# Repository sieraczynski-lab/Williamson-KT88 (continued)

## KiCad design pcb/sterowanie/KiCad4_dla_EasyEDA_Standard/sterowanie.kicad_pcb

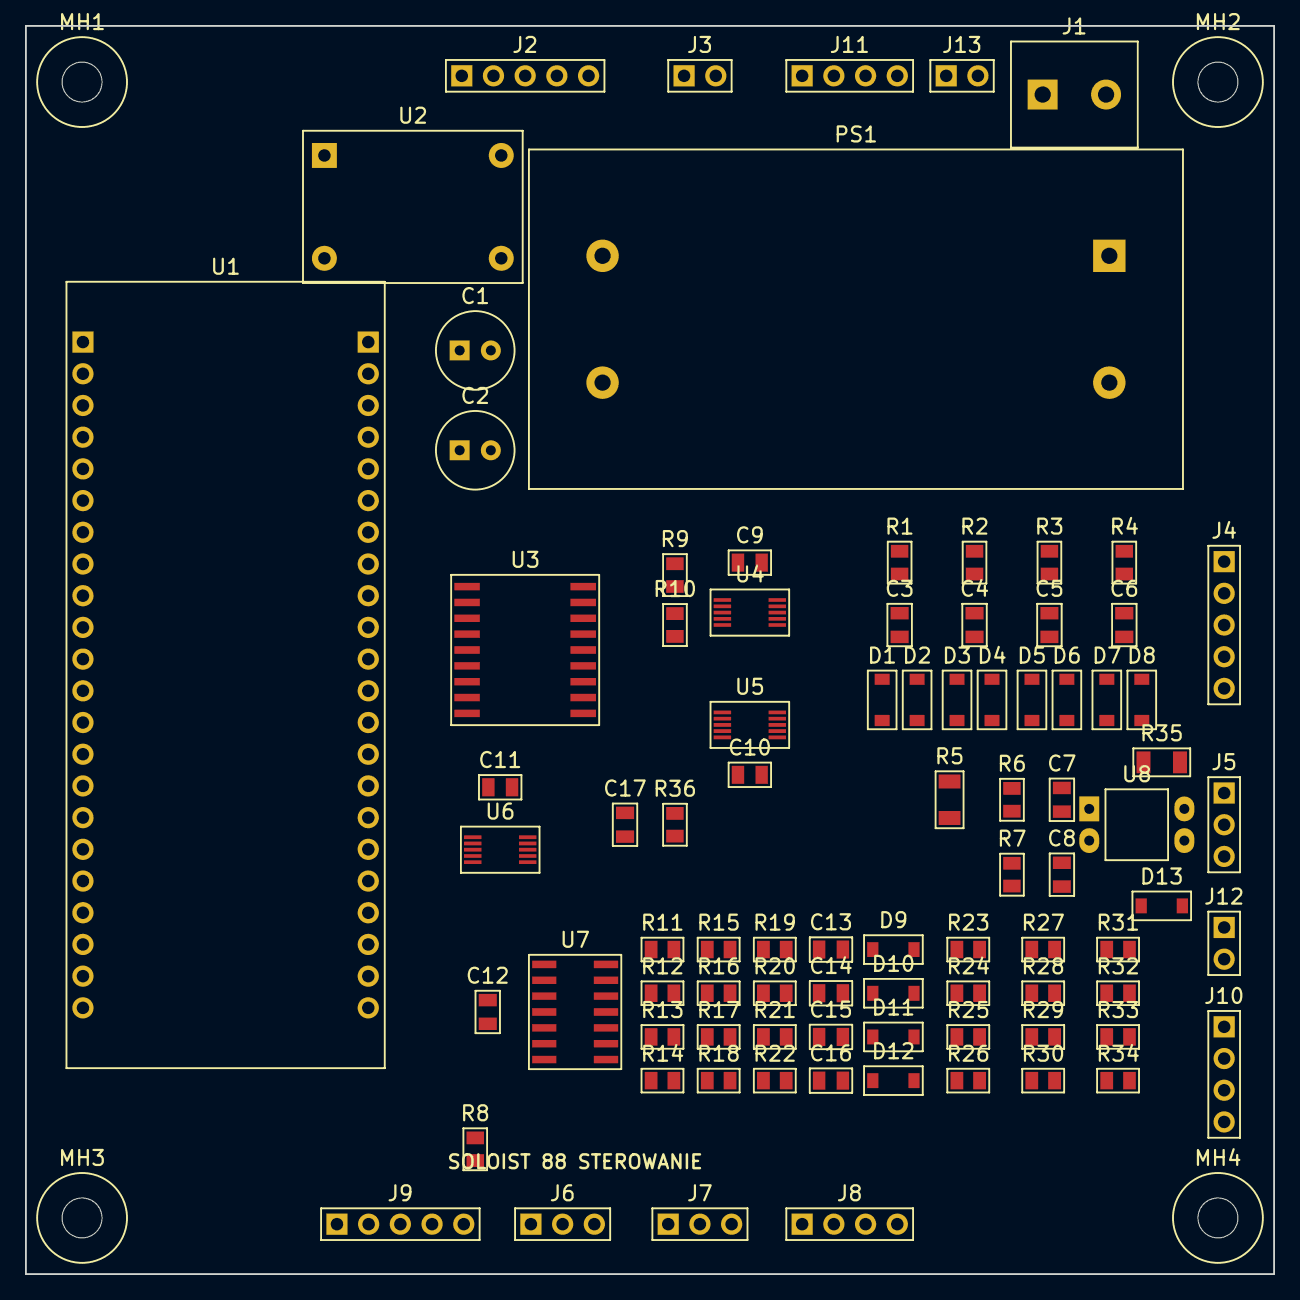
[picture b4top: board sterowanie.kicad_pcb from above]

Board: 2 copper layers, 100.0 x 100.0 mm, 92 parts (0 on the bottom side), 68 nets, no tracks yet.

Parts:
C1: 100u/25V; CP_Radial_D6.3_P2.5
C2: 100u/16V; CP_Radial_D6.3_P2.5
C3, C4, C5, C6, C7, C8: 1u; C_0805_2012Metric_V
C9, C10, C11: 100n; C_0805_2012Metric
C12, C17: 100n; C_0805_2012Metric_V
C13, C14, C15, C16: 1u; C_0805_2012Metric
D1, D2, D3, D4, D5, D6, D7, D8: 1N4148W; D_SOD-123_V
D9, D10, D11, D12, D13: 1N4148W; D_SOD-123
J1: 230V_IN; TerminalBlock_1x02_P5.08
J2: RELAY; PinHeader_1x05_P2.54_H
J3: MUTE; PinHeader_1x02_P2.54_H
J4: IK; PinHeader_1x05_P2.54
J5: SENSE; PinHeader_1x03_P2.54
J6: DS18B20; PinHeader_1x03_P2.54_H
J7: IR; PinHeader_1x03_P2.54_H
J8: WYSWIETLACZ; PinHeader_1x04_P2.54_H
J9: ENKODER; PinHeader_1x05_P2.54_H
J10: BIAS_KOR; PinHeader_1x04_P2.54
J11: UL_TRIODA; PinHeader_1x04_P2.54_H
J12: TRIGGER; PinHeader_1x02_P2.54
J13: GLOSNIKI; PinHeader_1x02_P2.54_H
MH1, MH2, MH3, MH4: M3; MountingHole_M3
PS1: IRM-15-12; MeanWell_IRM-15_approx
R1, R2, R3, R4, R6, R7, R36: 10k; R_0805_2012Metric_V
R5: 330k 1206; R_1206_3216Metric_V
R8, R9, R10: 4k7; R_0805_2012Metric_V
R11, R12, R13, R14, R19, R20, R21, R22: 10k; R_0805_2012Metric
R15, R16, R17, R18: 20k; R_0805_2012Metric
R23, R24, R25, R26: 68k; R_0805_2012Metric
R27, R28, R29, R30: 33k; R_0805_2012Metric
R31, R32, R33, R34: 1k; R_0805_2012Metric
R35: 1k 1206; R_1206_3216Metric
U1: ESP32-S3-DevKitC-1
U2: DC-DC 5V mini; DCDC_5V_mini_14.17x8.24
U3: ULN2803G-S18-R; SOIC-18W_7.5x11.6mm_P1.27mm
U4: ADS1115IDGSR 0x48; MSOP-10_3x3mm_P0.5mm
U5: ADS1115IDGSR 0x49; MSOP-10_3x3mm_P0.5mm
U6: MCP4728-E/UN; MSOP-10_3x3mm_P0.5mm
U7: LM324DR; SOIC-14_3.9x8.7mm_P1.27mm
U8: PC817; DIP-4_W7.62

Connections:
3V3: C9.1, C10.1, C11.1, D2.1, D4.1, D6.1, D8.1, J6.1, J7.1, J8.1, R6.2, R8.1, R9.1, R10.1, R36.1, U1.L1, U1.L2, U4.8, U5.1, U5.5, U5.8, U6.1
+5V: C2.1, U1.L21, U2.3
+12V: C1.1, C12.1, J2.1, J3.1, J11.1, J11.3, J13.1, PS1.4, U2.2, U3.10, U7.4
BI_L1: J10.1, R31.2
BI_L2: J10.2, R32.2
BI_R1: J10.3, R33.2
BI_R2: J10.4, R34.2
BTN: J9.4, U1.L9
DACF_L1: C13.1, R19.2, U7.3
DACF_L2: C14.1, R20.2, U7.5
DACF_R1: C15.1, R21.2, U7.10
DACF_R2: C16.1, R22.2, U7.12
DAC_L1: R19.1, U6.6
DAC_L2: R20.1, U6.7
DAC_R1: R21.1, U6.8
DAC_R2: R22.1, U6.9
DQ: J6.2, R8.2, U1.L4
DRV1: U1.L16, U3.1
DRV2: U1.L17, U3.2
DRV3: U1.L18, U3.3
DRV4: U1.L19, U3.4
DRV5: U1.L20, U3.5
DRV6: U1.L10, U3.6
DRV7: U1.L11, U3.7
ENC_A: J9.1, U1.L6
ENC_B: J9.2, U1.L7
ENC_SW: J9.3, U1.L8
FB_L1: R11.1, R15.2, U7.2
FB_L2: R12.1, R16.2, U7.6
FB_R1: R13.1, R17.2, U7.9
FB_R2: R14.1, R18.2, U7.13
GND: C1.2, C2.2, C3.2, C4.2, C5.2, C6.2, C7.2, C8.2, C9.2, C10.2, C11.2, C12.2, C13.2, C14.2, C15.2, C16.2, C17.2, D1.2, D3.2, D5.2, D7.2, D9.2, D10.2, D11.2, D12.2, J4.5, J5.3, J6.3, J7.3, J8.2, J9.5, PS1.3, R11.2, R12.2, R13.2, R14.2, U1.L22, U1.R1, U1.R21, U1.R22, U2.1, U2.4, U3.8, U3.9, U4.1, U4.3, U5.3, U6.4, U6.10, U7.11, U8.3
HV_F: C8.1, R7.2, U5.6
HV_SENSE: J5.2, R7.1
IK_L1: J4.1, R1.1
IK_L1F: C3.1, D1.1, D2.2, R1.2, U4.4
IK_L2: J4.2, R2.1
IK_L2F: C4.1, D3.1, D4.2, R2.2, U4.5
IK_R1: J4.3, R3.1
IK_R1F: C5.1, D5.1, D6.2, R3.2, U4.6
IK_R2: J4.4, R4.1
IK_R2F: C6.1, D7.1, D8.2, R4.2, U4.7
IR: J7.2, U1.L5
L_PS: J1.1, PS1.1
MUTE: J3.2, U3.14
N_PS: J1.2, PS1.2
OA_L1: D9.1, R15.1, R23.1, U7.1
OA_L2: D10.1, R16.1, R24.1, U7.7
OA_R1: D11.1, R17.1, R25.1, U7.8
OA_R2: D12.1, R18.1, R26.1, U7.14
OPTO_A: D13.1, R35.2, U8.1
RLY1: J2.2, U3.18
RLY2: J2.3, U3.17
RLY3: J2.4, U3.16
RLY4: J2.5, U3.15
RLY_SPK: J13.2, U3.12
RLY_UL: J11.2, J11.4, U3.13
SCL: J8.3, R10.2, U1.L15, U4.10, U5.10, U6.2
SDA: J8.4, R9.2, U1.L12, U4.9, U5.9, U6.3
S_L1: R23.2, R27.1, R31.1
S_L2: R24.2, R28.1, R32.1
S_R1: R25.2, R29.1, R33.1
S_R2: R26.2, R30.1, R34.1
TRIG_IN: C17.1, R36.2, U1.R4, U8.4
TRIG_N: D13.2, J12.2, U8.2
TRIG_P: J12.1, R35.1
VBIAS: J5.1, R5.1, R27.2, R28.2, R29.2, R30.2
VB_F: C7.1, R5.2, R6.1, U5.4

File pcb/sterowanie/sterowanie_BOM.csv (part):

Oznaczenie;Wartosc;Footprint;Strona;X [mm];Y [mm];Grupa;LCSC;Uwagi
U1;ESP32-S3-DevKitC-1;ESP32-S3-DevKitC-1;GORA;16.00;52.00;ESP32;;na listwach zenskich
J1;230V_IN;TerminalBlock_1x02_P5.08;GORA;84.00;5.50;ZASILANIE 12 V / 5 V;;zlacze srubowe 230 V: z zasilacz_siec J3 (za F2)
PS1;IRM-15-12;MeanWell_IRM-15_approx;GORA;66.50;23.50;ZASILANIE 12 V / 5 V;;Mean Well IRM-15-12, 12 V / 1,25 A
U2;DC-DC 5V mini;DCDC_5V_mini_14.17x8.24;GORA;31.00;14.50;ZASILANIE 12 V / 5 V;;"mini przetwornica step-down, stale 5 V, min. 1 A; 1 -IN, 2 +IN, 3 OUT+, 4 OUT-"
C1;100u/25V;CP_Radial_D6.3_P2.5;GORA;36.00;26.00;ZASILANIE 12 V / 5 V;;
C2;100u/16V;CP_Radial_D6.3_P2.5;GORA;36.00;34.00;ZASILANIE 12 V / 5 V;;
U3;ULN2803G-S18-R;SOIC-18W_7.5x11.6mm_P1.27mm;GORA;40.00;50.00;STEROWNIK PRZEKAZNIKOW;C33924;UTC ULN2803G-S18-R, SOP-18 (7,5 mm) - LCSC C33924
J2;RELAY;PinHeader_1x05_P2.54_H;GORA;40.00;4.00;STEROWNIK PRZEKAZNIKOW;;"do plytek zasilacza (piny 1,2,3 -> siec; 1,4,5 -> HV)"
J3;MUTE;PinHeader_1x02_P2.54_H;GORA;54.00;4.00;STEROWNIK PRZEKAZNIKOW;;przekaznik MUTE w przedwzmacniaczu
J11;UL_TRIODA;PinHeader_1x04_P2.54_H;GORA;66.00;4.00;STEROWNIK PRZEKAZNIKOW;;1-2 plytka UL kanalu L, 3-4 kanalu P (J3 na plytce UL)
J13;GLOSNIKI;PinHeader_1x02_P2.54_H;GORA;75.00;4.00;STEROWNIK PRZEKAZNIKOW;;cewki przelacznika glosnikow (plytka glosniki J7)
J12;TRIGGER;PinHeader_1x02_P2.54;GORA;96.00;73.50;WEJSCIE TRIGGER 12 V;;z gniazda jack 3,5 mm na tylnej sciance (izolowanego od obudowy): 1 koncowka (+12 V), 2 tulejka
R35;1k 1206;R_1206_3216Metric;GORA;91.00;59.00;WEJSCIE TRIGGER 12 V;C4410;ok. 10 mA przy 12 V
D13;1N4148W;D_SOD-123;GORA;91.00;70.50;WEJSCIE TRIGGER 12 V;C81598;ochrona przed odwrotna polaryzacja
U8;PC817;DIP-4_W7.62;GORA;89.00;64.00;WEJSCIE TRIGGER 12 V;;transoptor - masa Marantza oddzielona od masy Lampy
R36;10k;R_0805_2012Metric_V;GORA;52.00;64.00;WEJSCIE TRIGGER 12 V;C17414;"podciaganie; TRIG_IN = 0 gdy trigger aktywny"
C17;100n;C_0805_2012Metric_V;GORA;48.00;64.00;WEJSCIE TRIGGER 12 V;C49678;filtr zaklocen
U4;ADS1115IDGSR 0x48;MSOP-10_3x3mm_P0.5mm;GORA;58.00;47.00;POMIARY ADC;C37593;ADDR do GND
U5;ADS1115IDGSR 0x49;MSOP-10_3x3mm_P0.5mm;GORA;58.00;56.00;POMIARY ADC;C37593;ADDR do VDD
C9;100n;C_0805_2012Metric;GORA;58.00;43.00;POMIARY ADC;C49678;przy U4
C10;100n;C_0805_2012Metric;GORA;58.00;60.00;POMIARY ADC;C49678;przy U5
R9;4k7;R_0805_2012Metric_V;GORA;52.00;44.00;POMIARY ADC;C17673;podciaganie I2C
R10;4k7;R_0805_2012Metric_V;GORA;52.00;48.00;POMIARY ADC;C17673;podciaganie I2C
U6;MCP4728-E/UN;MSOP-10_3x3mm_P0.5mm;GORA;38.00;66.00;KOREKTA BIASU (DAC);C108207;"I2C 0x60, Vref = VDD 3,3 V; LDAC do masy"
C11;100n;C_0805_2012Metric;GORA;38.00;61.00;KOREKTA BIASU (DAC);C49678;przy U6
U7;LM324DR;SOIC-14_3.9x8.7mm_P1.27mm;GORA;44.00;79.00;KOREKTA BIASU (DAC);C7943;wzmocnienie x3: 0-3,3 V -> 0-9,9 V
C12;100n;C_0805_2012Metric_V;GORA;37.00;79.00;KOREKTA BIASU (DAC);C49678;przy U7
R1;10k;R_0805_2012Metric_V;GORA;70.00;43.00;FILTRY WEJSC;C17414;
C3;1u;C_0805_2012Metric_V;GORA;70.00;48.00;FILTRY WEJSC;C28323;X7R 50 V
D1;1N4148W;D_SOD-123_V;GORA;68.60;54.00;FILTRY WEJSC;C81598;zacisk do masy
D2;1N4148W;D_SOD-123_V;GORA;71.40;54.00;FILTRY WEJSC;C81598;zacisk do 3V3
R2;10k;R_0805_2012Metric_V;GORA;76.00;43.00;FILTRY WEJSC;C17414;
C4;1u;C_0805_2012Metric_V;GORA;76.00;48.00;FILTRY WEJSC;C28323;X7R 50 V
D3;1N4148W;D_SOD-123_V;GORA;74.60;54.00;FILTRY WEJSC;C81598;zacisk do masy
D4;1N4148W;D_SOD-123_V;GORA;77.40;54.00;FILTRY WEJSC;C81598;zacisk do 3V3
R3;10k;R_0805_2012Metric_V;GORA;82.00;43.00;FILTRY WEJSC;C17414;
C5;1u;C_0805_2012Metric_V;GORA;82.00;48.00;FILTRY WEJSC;C28323;X7R 50 V
D5;1N4148W;D_SOD-123_V;GORA;80.60;54.00;FILTRY WEJSC;C81598;zacisk do masy
D6;1N4148W;D_SOD-123_V;GORA;83.40;54.00;FILTRY WEJSC;C81598;zacisk do 3V3
R4;10k;R_0805_2012Metric_V;GORA;88.00;43.00;FILTRY WEJSC;C17414;
C6;1u;C_0805_2012Metric_V;GORA;88.00;48.00;FILTRY WEJSC;C28323;X7R 50 V
D7;1N4148W;D_SOD-123_V;GORA;86.60;54.00;FILTRY WEJSC;C81598;zacisk do masy
D8;1N4148W;D_SOD-123_V;GORA;89.40;54.00;FILTRY WEJSC;C81598;zacisk do 3V3
R11;10k;R_0805_2012Metric;GORA;51.00;74.00;KOREKTA BIASU (DAC);C17414;wzmocnienie
R15;20k;R_0805_2012Metric;GORA;55.50;74.00;KOREKTA BIASU (DAC);C4328;wzmocnienie
R19;10k;R_0805_2012Metric;GORA;60.00;74.00;KOREKTA BIASU (DAC);C17414;filtr RC przed LM324 (10k / 1u = 10 ms)
C13;1u;C_0805_2012Metric;GORA;64.50;74.00;KOREKTA BIASU (DAC);C28323;filtr RC
D9;1N4148W;D_SOD-123;GORA;69.50;74.00;KOREKTA BIASU (DAC);C81598;zacisk wyjscia LM324: bez 12 V nie schodzi ponizej masy
R23;68k;R_0805_2012Metric;GORA;75.50;74.00;KOREKTA BIASU (DAC);C17801;przesuwnik poziomu (0-9,9 V -> ok. -54...-51 V)
R27;33k;R_0805_2012Metric;GORA;81.50;74.00;KOREKTA BIASU (DAC);C17633;przesuwnik poziomu, do szyny biasu
R31;1k;R_0805_2012Metric;GORA;87.50;74.00;KOREKTA BIASU (DAC);C17513;wyjscie do wezla biasu (ochrona przy zwarciu przewodu)
R12;10k;R_0805_2012Metric;GORA;51.00;77.50;KOREKTA BIASU (DAC);C17414;wzmocnienie
R16;20k;R_0805_2012Metric;GORA;55.50;77.50;KOREKTA BIASU (DAC);C4328;wzmocnienie
R20;10k;R_0805_2012Metric;GORA;60.00;77.50;KOREKTA BIASU (DAC);C17414;filtr RC przed LM324 (10k / 1u = 10 ms)
C14;1u;C_0805_2012Metric;GORA;64.50;77.50;KOREKTA BIASU (DAC);C28323;filtr RC
D10;1N4148W;D_SOD-123;GORA;69.50;77.50;KOREKTA BIASU (DAC);C81598;zacisk wyjscia LM324: bez 12 V nie schodzi ponizej masy
R24;68k;R_0805_2012Metric;GORA;75.50;77.50;KOREKTA BIASU (DAC);C17801;przesuwnik poziomu (0-9,9 V -> ok. -54...-51 V)
R28;33k;R_0805_2012Metric;GORA;81.50;77.50;KOREKTA BIASU (DAC);C17633;przesuwnik poziomu, do szyny biasu
R32;1k;R_0805_2012Metric;GORA;87.50;77.50;KOREKTA BIASU (DAC);C17513;wyjscie do wezla biasu (ochrona przy zwarciu przewodu)
R13;10k;R_0805_2012Metric;GORA;51.00;81.00;KOREKTA BIASU (DAC);C17414;wzmocnienie
R17;20k;R_0805_2012Metric;GORA;55.50;81.00;KOREKTA BIASU (DAC);C4328;wzmocnienie
R21;10k;R_0805_2012Metric;GORA;60.00;81.00;KOREKTA BIASU (DAC);C17414;filtr RC przed LM324 (10k / 1u = 10 ms)
C15;1u;C_0805_2012Metric;GORA;64.50;81.00;KOREKTA BIASU (DAC);C28323;filtr RC
D11;1N4148W;D_SOD-123;GORA;69.50;81.00;KOREKTA BIASU (DAC);C81598;zacisk wyjscia LM324: bez 12 V nie schodzi ponizej masy
R25;68k;R_0805_2012Metric;GORA;75.50;81.00;KOREKTA BIASU (DAC);C17801;przesuwnik poziomu (0-9,9 V -> ok. -54...-51 V)
R29;33k;R_0805_2012Metric;GORA;81.50;81.00;KOREKTA BIASU (DAC);C17633;przesuwnik poziomu, do szyny biasu
R33;1k;R_0805_2012Metric;GORA;87.50;81.00;KOREKTA BIASU (DAC);C17513;wyjscie do wezla biasu (ochrona przy zwarciu przewodu)
R14;10k;R_0805_2012Metric;GORA;51.00;84.50;KOREKTA BIASU (DAC);C17414;wzmocnienie
R18;20k;R_0805_2012Metric;GORA;55.50;84.50;KOREKTA BIASU (DAC);C4328;wzmocnienie
R22;10k;R_0805_2012Metric;GORA;60.00;84.50;KOREKTA BIASU (DAC);C17414;filtr RC przed LM324 (10k / 1u = 10 ms)
C16;1u;C_0805_2012Metric;GORA;64.50;84.50;KOREKTA BIASU (DAC);C28323;filtr RC
D12;1N4148W;D_SOD-123;GORA;69.50;84.50;KOREKTA BIASU (DAC);C81598;zacisk wyjscia LM324: bez 12 V nie schodzi ponizej masy
R26;68k;R_0805_2012Metric;GORA;75.50;84.50;KOREKTA BIASU (DAC);C17801;przesuwnik poziomu (0-9,9 V -> ok. -54...-51 V)
R30;33k;R_0805_2012Metric;GORA;81.50;84.50;KOREKTA BIASU (DAC);C17633;przesuwnik poziomu, do szyny biasu
R34;1k;R_0805_2012Metric;GORA;87.50;84.50;KOREKTA BIASU (DAC);C17513;wyjscie do wezla biasu (ochrona przy zwarciu przewodu)
R5;330k 1206;R_1206_3216Metric_V;GORA;74.00;62.00;FILTRY WEJSC;C17929;pomiar -78 V
R6;10k;R_0805_2012Metric_V;GORA;79.00;62.00;FILTRY WEJSC;C17414;przesuniecie do 3V3
C7;1u;C_0805_2012Metric_V;GORA;83.00;62.00;FILTRY WEJSC;C28323;
R7;10k;R_0805_2012Metric_V;GORA;79.00;68.00;FILTRY WEJSC;C17414;
C8;1u;C_0805_2012Metric_V;GORA;83.00;68.00;FILTRY WEJSC;C28323;
R8;4k7;R_0805_2012Metric_V;GORA;36.00;90.00;ESP32;C17673;pull-up DS18B20
J4;IK;PinHeader_1x05_P2.54;GORA;96.00;48.00;ZLACZA;;z rezystorow 10R przy KT88
J5;SENSE;PinHeader_1x03_P2.54;GORA;96.00;64.00;ZLACZA;;
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
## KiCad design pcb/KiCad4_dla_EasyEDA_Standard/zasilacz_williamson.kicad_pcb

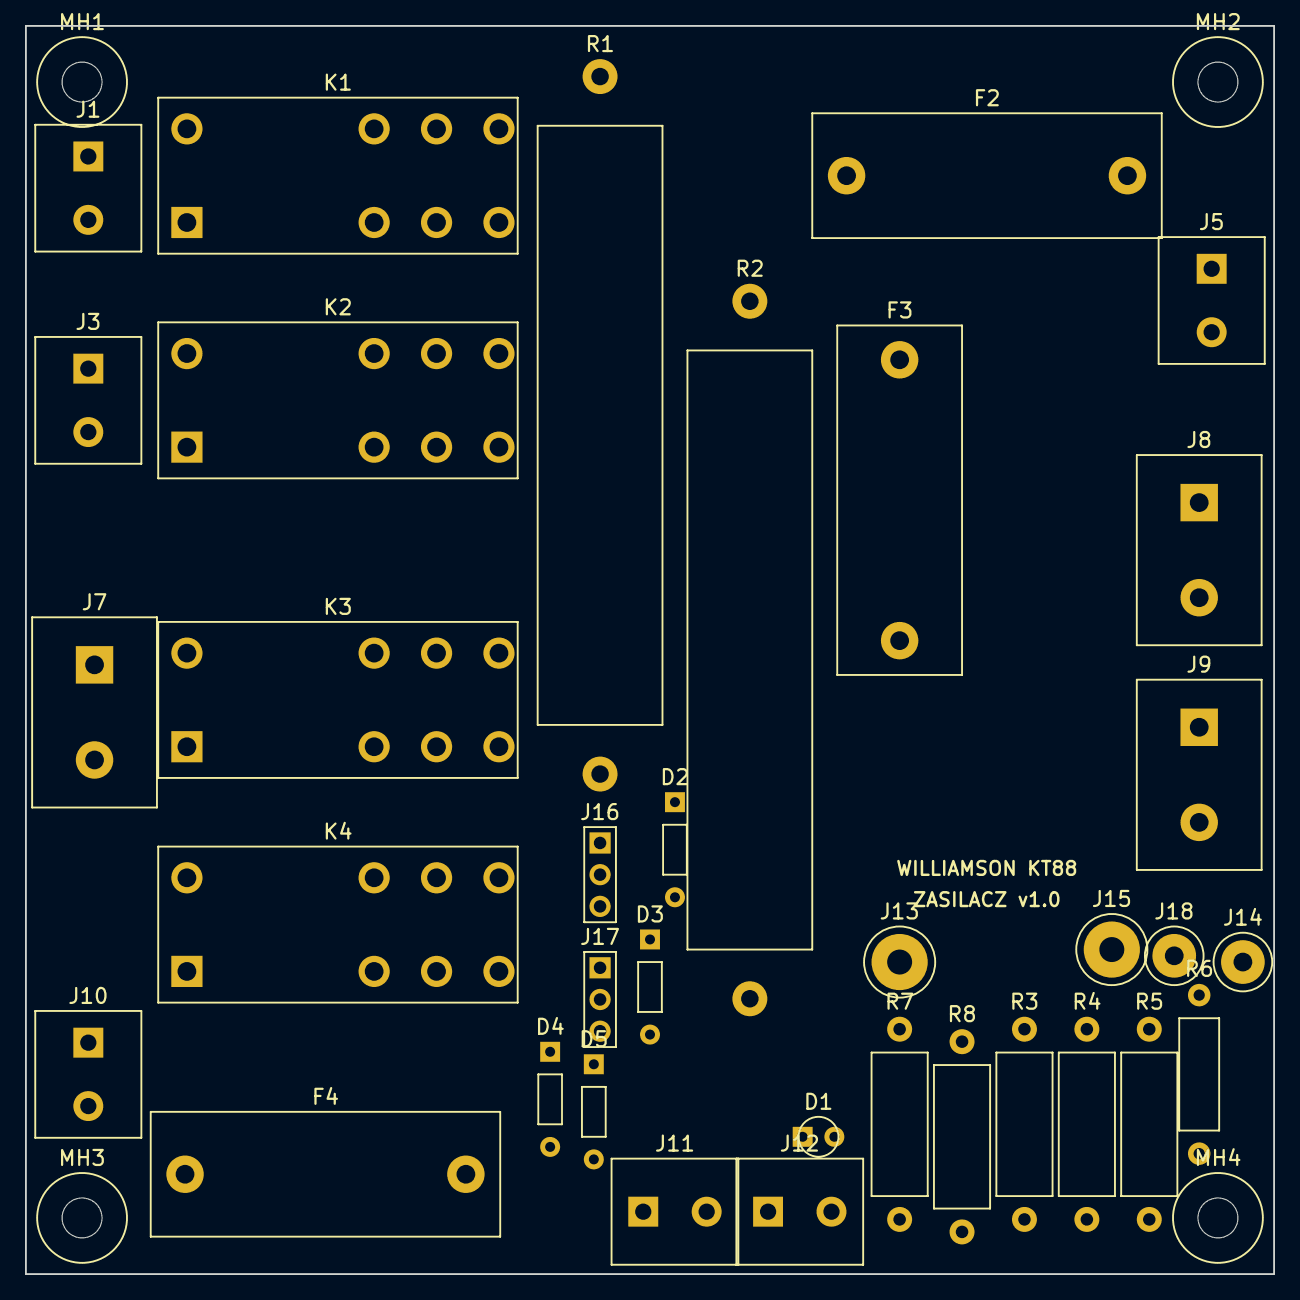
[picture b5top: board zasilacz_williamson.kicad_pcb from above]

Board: 2 copper layers, 100.0 x 100.0 mm, 39 parts (0 on the bottom side), 26 nets, no tracks yet.

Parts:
D1: LED HV czerwona; LED_D3.0_P2.54
D2, D3, D4, D5: 1N4148; D_DO-35_P7.62_V
F2: T500mA 250V; Fuseholder_5x20_Closed_P22.5
F3: T1A 500V; Fuseholder_5x20_Closed_P22.5_V
F4: T100mA 250V; Fuseholder_5x20_Closed_P22.5
J1: SIEC; TerminalBlock_1x02_P5.08_V
J3: PS1; TerminalBlock_1x02_P5.08_V
J5: TR1_PRI; TerminalBlock_1x02_P5.08_V
J7: S1_IN; TerminalBlock_1x02_P7.62_V
J8: HT_L; TerminalBlock_1x02_P7.62_V
J9: HT_R; TerminalBlock_1x02_P7.62_V
J10: S4_IN; TerminalBlock_1x02_P5.08_V
J11: BIAS_L; TerminalBlock_1x02_P5.08
J12: BIAS_R; TerminalBlock_1x02_P5.08
J13: UA_IN; WirePad_4.5
J14: HV_SENSE; WirePad_3.5
J15: GND_ONYX; WirePad_4.5
J16: RELAY_A; PinHeader_1x03_P2.54
J17: RELAY_B; PinHeader_1x03_P2.54
J18: GND_STER; WirePad_3.5
K1, K2, K3, K4: G2RL-2-DC12; Relay_DPDT_Omron_G2RL
MH1, MH2, MH3, MH4: M3; MountingHole_M3
R1: 47R 10W; R_Cement_10W_P55.88_V
R2: 100R 10W; R_Cement_10W_P55.88_V
R3, R4, R5: 1M 1600V; R_Axial_1W_P15.24_V
R6: 15k; R_Axial_0.5W_P12.7_V
R7, R8: 220k 1W; R_Axial_1W_P15.24_V

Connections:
+12V: D2.1, D3.1, D4.1, D5.1, J16.1, J17.1, K1.1, K2.1, K3.1, K4.1
B_AC1: F4.1, J10.1
B_AC2: J10.2, J11.2, J12.2
B_F: F4.2, J11.1, J12.1
GND: D1.1, J15.1, J18.1, R6.2
HT_B: J7.2, J8.2, J9.2
HT_F: F3.2, K3.3
HT_IN: J8.1, J9.1, K4.4, K4.5, R2.2
HT_K3: K3.5, K4.3, K4.6, R2.1
HT_TR: F3.1, J7.1
HVS1: R3.2, R4.1
HVS2: R4.2, R5.1
HV_SENSE: J14.1, R5.2, R6.1
K3_MID: K3.4, K3.6
LED_A: D1.2, R8.2
LED_M: R7.2, R8.1
L_K1: K1.4, K1.5, K2.3, K2.6, R1.1
L_SW: F2.2, J1.1, K1.3, K1.6
L_TR: J5.1, K2.4, K2.5, R1.2
L_TR2: F2.1, J3.1
N_SW: J1.2, J3.2, J5.2
RLY1: D2.2, J16.2, K1.8
RLY2: D3.2, J16.3, K2.8
RLY3: D4.2, J17.2, K3.8
RLY4: D5.2, J17.3, K4.8
UA: J13.1, R3.1, R7.1

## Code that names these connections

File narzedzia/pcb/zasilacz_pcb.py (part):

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        ("R2", "100R 10W", "R", ["HT_K3", "HT_IN"], g_ht, "R_IN: udar ladowania kondensatorow Onyxa ok. 5 A"),
        ("K4", "G2RL-2-DC12", "RELAY_G2RL", {"1": "+12V", "8": "RLY4", "3": "HT_K3", "6": "HT_K3", "4": "HT_IN", "5": "HT_IN", "2": None, "7": None}, g_ht,
         "bocznik R_IN (+1,5 s); 2 styki rownolegle"),
        ("J8", "HT_L", "CONN_2", ["HT_IN", "HT_B"], g_ht, "zlacze srubowe 7,62 mm: do Onyx J103 (1 -> pin 1, 2 -> pin 2)"),
        ("J9", "HT_R", "CONN_2", ["HT_IN", "HT_B"], g_ht, "zlacze srubowe 7,62 mm: do Onyx J203"),
        # ---- bias ----
        ("J10", "S4_IN", "CONN_2", ["B_AC1", "B_AC2"], g_b, "zlacze srubowe: S4 58 V z TR1"),
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        ("R4", "1M 1600V", "R", ["HVS1", "HVS2"], g_s, ""),
        ("R5", "1M 1600V", "R", ["HVS2", "HV_SENSE"], g_s, ""),
        ("R6", "15k", "R", ["HV_SENSE", "GND"], g_s, "ok. 2,3 V przy 465 V"),
        ("J14", "HV_SENSE", "PAD", ["HV_SENSE"], g_s, "do sterowania J5 pin 2"),
        ("J15", "GND_ONYX", "PAD", ["GND"], g_c, "masa: do gwiazdy na plytce Onyxa (minus C120)"),
        ("J18", "GND_STER", "PAD", ["GND"], g_c, "masa pomiaru: do sterowania J5"),
        # ---- LED HV ----
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        ("R8", "220k 1W", "R", ["LED_M", "LED_A"], g_l, ""),
        ("D1", "LED HV czerwona", "D", {"1": "GND", "2": "LED_A"}, g_l, "swieci, dopoki na plytce Onyxa jest napiecie; NIE ZASTEPUJE MIERNIKA"),
        # ---- cewki ----
        ("J16", "RELAY_A", "CONN_3", ["+12V", "RLY1", "RLY2"], g_r, "ze sterowania J2 piny 1,2,3"),
        ("J17", "RELAY_B", "CONN_3", ["+12V", "RLY3", "RLY4"], g_r, "ze sterowania J2 piny 1,4,5"),
        ("D2", "1N4148", "D", {"1": "+12V", "2": "RLY1"}, g_r, ""),
        ("D3", "1N4148", "D", {"1": "+12V", "2": "RLY2"}, g_r, ""),
        ("D4", "1N4148", "D", {"1": "+12V", "2": "RLY3"}, g_r, ""),
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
